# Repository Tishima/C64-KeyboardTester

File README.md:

# C64 Keyboard Tester

This small circuit is for testing C64 keyboards, it measure with a AVR uC ATTINY85 the resistance of a keypress.
under a treashold of 800Ohm - a red led goes on
a green led show a startet uC

so its possible to check if a key on the keyboard makes some trouble, the treshold is at 800 Ohm , a press on a C64 is mormaly detect under 1kOhm
the ATTINY85 works with internal clock at 1Mhz

This repository contains all Autodesk Eagle files, gerber file, BOM, schematics, a small Arduino source code, Hex File for ATTINY85, Projekt File for XGeco T48-3 Eprom Programmer for Firmware

STL and CAD Files for a minimal enclosure, 

Depending on where the parts and pcbs are purchased, the price for the complete circuit is around 5€ (2023), without enclosure and power supply

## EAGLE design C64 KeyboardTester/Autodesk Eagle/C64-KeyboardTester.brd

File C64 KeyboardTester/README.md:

# C64 Keyboard Tester
This small circuit is for testing C64 keyboards, it measure with a AVR uC ATTINY85 the resistance of a keypress.
under a treashold of 800Ohm - a red led goes on
a green led show a startet uC

so its possible to check if a key on the keyboard makes some trouble, the treshold is at 800 Ohm , a press on a C64 is mormaly detect under 1kOhm
the ATTINY85 works with internal clock at 1Mhz

This repository contains all Autodesk Eagle files, gerber file, BOM, schematics, a small Arduino source code, Hex File for ATTINY85, Projekt File for XGeco T48-3 Eprom Programmer for Firmware
STL and CAD Files for a minimal enclosure
Depending on where the parts and pcbs are purchased, the price for the complete circuit is around 5€ (2023), without enclosure and power supply

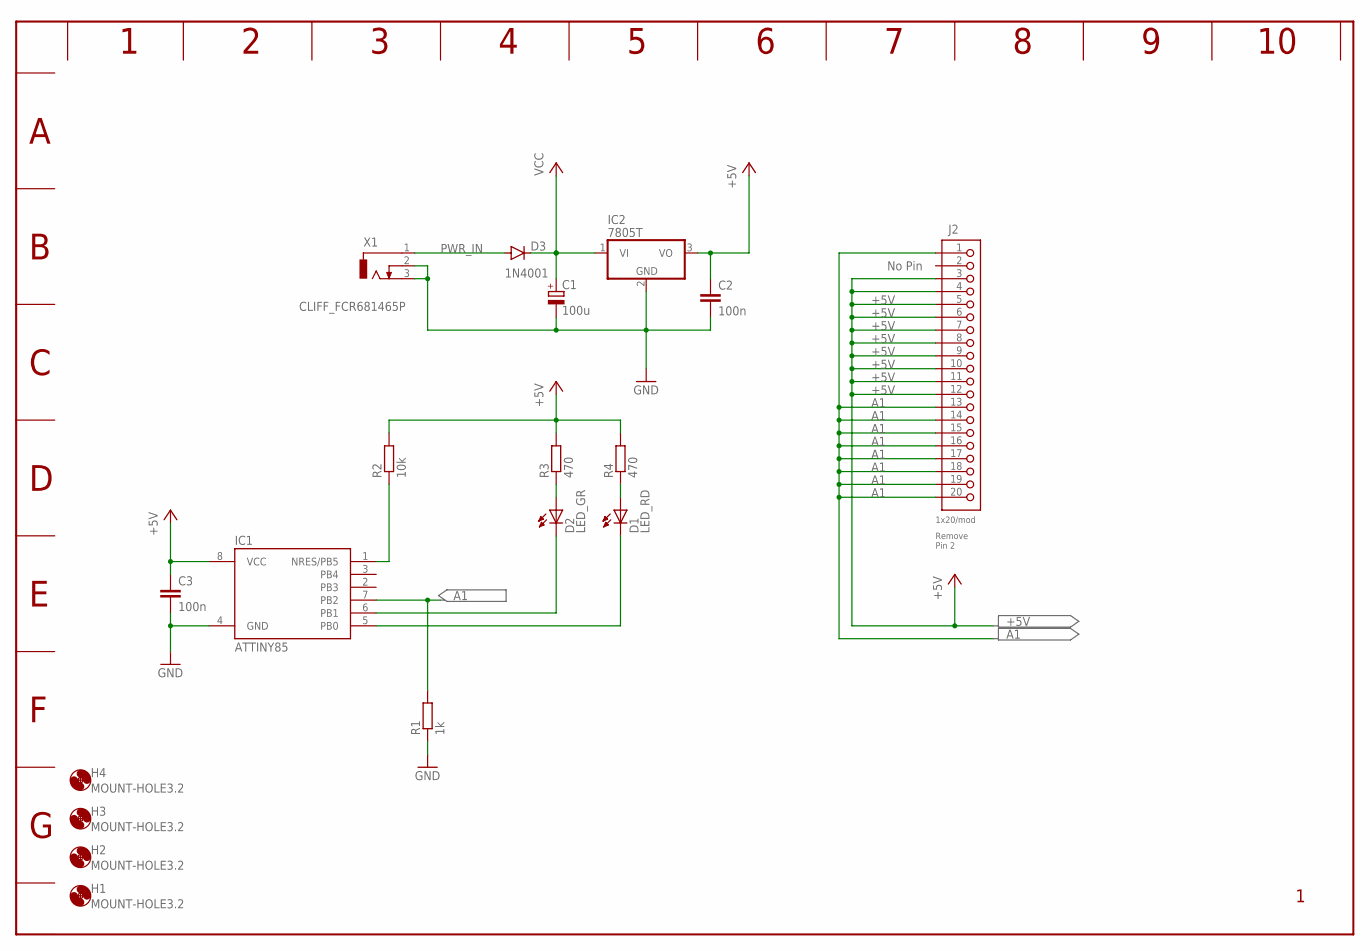
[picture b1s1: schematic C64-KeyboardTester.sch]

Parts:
C1: 100u; E2,5-6
C2, C3: 100n; C025-024X044
D1: LED_RD; LED3MM
D2: LED_GR; LED3MM
D3: 1N4001; DO41-10
H1, H2, H3, H4: MOUNT-HOLE3.2; 3,2
IC1: ATTINY85; PDIP08_300MIL
IC2: 7805T; TO220H
J2: 1x20/mod; 1X20
R1: 1k; 0207/10
R2: 10k; 0207/10
R3, R4: 470; 0207/10
X1: CLIFF_FCR681465P; FCR681465P

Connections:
+5V: C2.1, C3.1, IC1.8 (VCC), IC2.3 (VO), J2.3, J2.4, J2.5, J2.6, J2.7, J2.8, J2.9, J2.10, J2.11, J2.12, R2.2, R3.2, R4.2
A1: IC1.7 (PB2), J2.1, J2.13, J2.14, J2.15, J2.16, J2.17, J2.18, J2.19, J2.20, R1.2
GND: C1.-, C2.2, C3.2, IC1.4 (GND), IC2.2 (GND), R1.1, X1.2, X1.3
unnamed: D1.K (C), IC1.5 (PB0)
unnamed: D2.K (C), IC1.6 (PB1)
unnamed: IC1.1 (NRES/PB5), R2.1
unnamed: D2.A, R3.1
unnamed: D1.A, R4.1
PWR_IN: D3.A, X1.1
VCC: C1.+, D3.C, IC2.1 (VI)

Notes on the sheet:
No Pin
Remove Pin 2

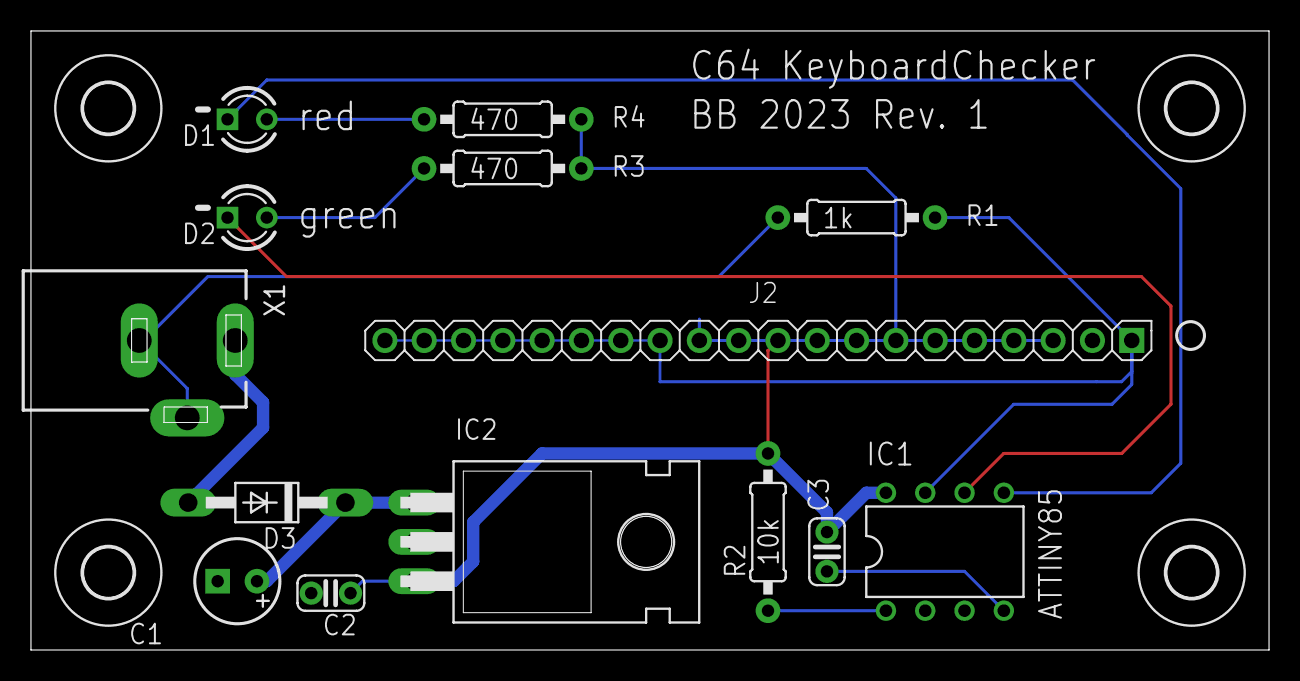
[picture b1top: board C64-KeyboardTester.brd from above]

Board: 2 copper layers, 80.0 x 40.0 mm, 18 parts (0 on the bottom side), 10 nets.
